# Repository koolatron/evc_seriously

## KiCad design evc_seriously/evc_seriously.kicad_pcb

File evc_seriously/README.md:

# evc_seriously

A seriously excessive VFD clock project

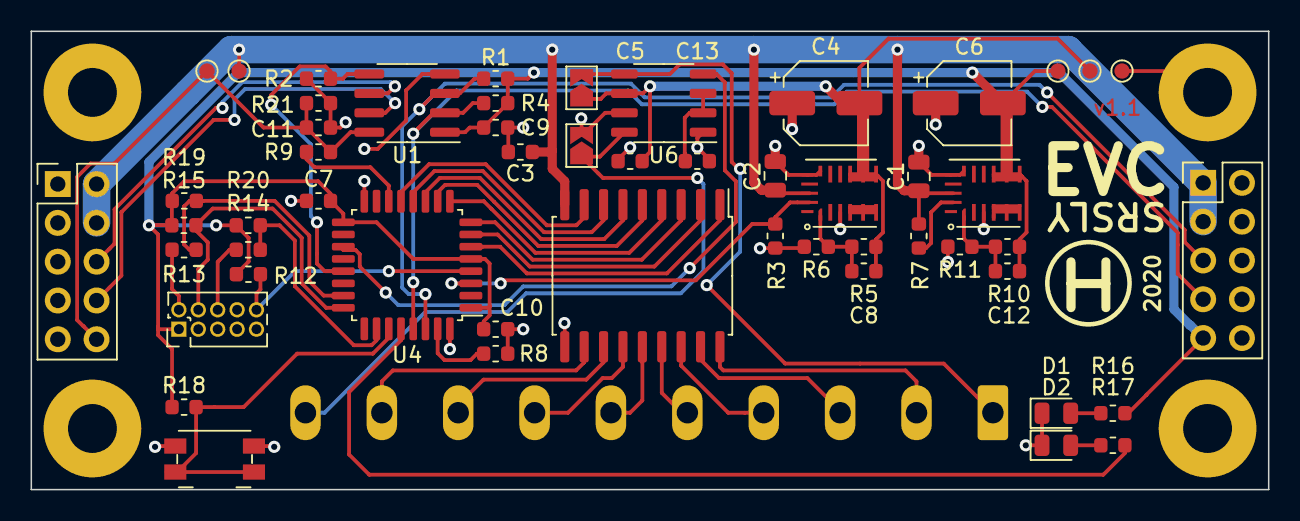
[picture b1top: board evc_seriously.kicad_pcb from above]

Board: 2 copper layers, 81.0 x 30.0 mm, 58 parts (1 on the bottom side), 48 nets.

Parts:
C1, C2: 4.7uF; C_0805_2012Metric
C3, C5, C7, C9, C10, C11: 0.1uF; C_0603_1608Metric
C4, C6: 22uF; CP_Elec_5x5.8
C8, C12: 22pF; C_0603_1608Metric
C13: 1uF; C_0603_1608Metric
D1, D2: LED; LED_0805_2012Metric
H1, H2, H3, H4: MountingHole_Pad; MountingHole_3.2mm_M3_Pad
J1: Screw_Terminal_01x10; PhoenixContact_MSTBVA_2,5_10-G_1x10_P5.00mm_Vertical
J2: Conn_ARM_JTAG_SWD_10; PinHeader_2x05_P1.27mm_Vertical
J3: J_IN; PinHeader_2x05_P2.54mm_Vertical
J4: J_OUT; PinHeader_2x05_P2.54mm_Vertical
JP1, JP2: SolderJumper_2_Open; SolderJumper-2_P1.3mm_Open_TrianglePad1.0x1.5mm
R1, R2, R3, R4, R8, R12, R15, R18, R19, R20, R21: 10k; R_0603_1608Metric
R5, R10: 75k; R_0603_1608Metric
R6: 14.3k; R_0603_1608Metric
R7: 1M; R_0603_1608Metric
R9, R13, R14: 22; R_0603_1608Metric
R11: 24k; R_0603_1608Metric
R16, R17: 660; R_0603_1608Metric
SW1: SW_Push; Panasonic_EVQPUK_EVQPUB
TP1, TP2, TP3, TP4, TP5: TestPoint; TestPoint_Pad_D1.0mm
U1: TCA9517; SOIC-8_3.9x4.9mm_P1.27mm
U2, U3: MPM3510A; QFN-19_3x5mm_P0.6mm
U4: STM32F303K8Tx; LQFP-32_7x7mm_P0.8mm
U5: MIC2981; SOIC-18W_7.5x11.6mm_P1.27mm
U6: LM9022; SO-8_3.9x4.9mm_P1.27mm

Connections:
+3V3: C6.2, C7.2, C9.2, C10.2, C12.1, J2.1, J3.9, R1.1, R4.1, R10.2, R12.1, R15.1, R16.2, R18.1, R19.1, R20.1, TP4.1, U1.1, U3.7, U3.8, U3.9, U4.1, U4.5, U4.17
+3V3_B: C11.2, J4.10, R9.2, R21.2, TP5.1, U1.8
+5V: C4.2, C5.2, C8.1, JP1.1, R5.2, TP3.1, U2.7, U2.8, U2.9, U6.6
+24V: C1.2, C2.2, C3.2, J3.1, J3.3, J4.2, J4.4, R7.2, TP1.1, U2.15, U3.15, U5.9
/5V_EN: R3.1, U2.16, U4.3
/FIL_PWM: U4.19, U6.4
/GRID: J1.9, U5.11
/I2C_EN: R2.1, U1.5, U4.21
/NRST: J2.10, R12.2, U4.4
/SCL_A: J3.7, R4.2, U1.2, U4.29
/SCL_B: J4.8, U1.7
/SDA_A: J3.5, R1.2, U1.3, U4.30
/SDA_B: J4.6, U1.6
/SEG_A: J1.2, U5.18
/SEG_B: J1.3, U5.17
/SEG_C: J1.4, U5.16
/SEG_D: J1.5, U5.15
/SEG_E: J1.6, U5.14
/SEG_F: J1.7, U5.13
/SEG_G: J1.8, U5.12
/SENSE: R9.1, U4.14
/SWDCLK: J2.4, R15.2, U4.24
/SWDIO: R13.1, R19.2, U4.23
/SWO: R14.1, R20.2, U4.26
/USR_LED: R17.2, U4.28
/USR_SW: R18.2, SW1.1, U4.27
/VFIL+: J1.1, JP1.2, U6.5
/VFIL-: J1.10, JP2.1, U6.8
GND: C1.1, C2.1, C3.1, C4.1, C5.1, C6.1, C7.1, C9.1, C10.1, C11.1, C13.1, D1.1, D2.1, H1.1, H2.1, H3.1, H4.1, J2.3, J2.5, J3.2, J3.4, J3.6, J3.8, J3.10, J4.1, J4.3, J4.5, J4.7, J4.9, JP2.2, R2.2, R3.2, R6.1, R8.2, R11.1, R21.1, SW1.2, TP2.1, U1.4, U2.3, U2.12, U2.13, U3.3, U3.12, U3.13, U4.16, U4.32, U5.10, U6.1, U6.7
unnamed: C8.2, R5.1, R6.2, U2.1
unnamed: C12.2, R10.1, R11.2, U3.1
unnamed: C13.2, U6.2, U6.3
unnamed: D1.2, R16.1
unnamed: D2.2, R17.1
unnamed: J2.2, R13.2
unnamed: J2.6, R14.2
unnamed: R7.1, U3.16
unnamed: R8.1, U4.31
unnamed: U2.4, U2.5, U2.6
unnamed: U3.4, U3.5, U3.6
unnamed: U4.6, U5.1
unnamed: U4.7, U5.2
unnamed: U4.8, U5.3
unnamed: U4.9, U5.4
unnamed: U4.10, U5.5
unnamed: U4.11, U5.6
unnamed: U4.12, U5.7
unnamed: U4.13, U5.8

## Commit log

2020-10-06 Add more library parts, add parts to schematic
    - Added a new project-level library to contain new parts:
    - MIC2981 source driver
    - LM9022 filament driver
    - TCA9517 I2C bus repeater
2020-10-10 Majority of schematic capture complete
2020-10-11 Finish schematic capture
    - Can I interest you in some capacitors?
    - Perhaps some pullup/pulldowns?
2020-10-11 Minor changes to please ERC
2020-10-11 Tidy schematic
    I'm really just stalling to avoid creating footprints
2020-10-13 Add final footprints, begin routing board
    Assign footprints to components, tune up some footprints/symbols
    Add missing footprint for MPM3510A
    Start placing components and routing board
    HOLY CATS that buck regulator part was a pain to create a footprint for!
2020-10-14 More routing of the board
2020-10-18 Start routing nets
    - Routed GND, +5V, and some +3V3
    - TODO: swap positions of 3V3 and 5V bucks to simplify power bus
2020-10-19 More routing
    - Finish routing power nets
    - Start routing data/enable lines
    - Swap a bunch of microcontroller pins to reduce hopping
2020-10-19 More routing
    - Swapped position of 3V3 and 5V buck converters
    - Finish routing power nets
    - Start routing data/enable lines
    - Swap a bunch of microcontroller pins to reduce hopping
2020-10-20 Finish board routing, tidy silkscreen
2020-10-20 Fix regulator fill zones (but not really)
2020-11-01 Fix silkscreen, add bling
2020-11-01 Add fab outputs
2021-01-31 Final changes for rev 1.1
